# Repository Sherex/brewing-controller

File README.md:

# Brewing controller
A board to control a brewing-rig.

## Images
Temprature sensor ADCs and connectors to the TP100 elemts

230V current sensing, relay control and 230V to 12V/5V tranformer

3D render of temprature ADCs and connectors

## Development
Requires [KiCad EDA](https://kicad-pcb.org/)

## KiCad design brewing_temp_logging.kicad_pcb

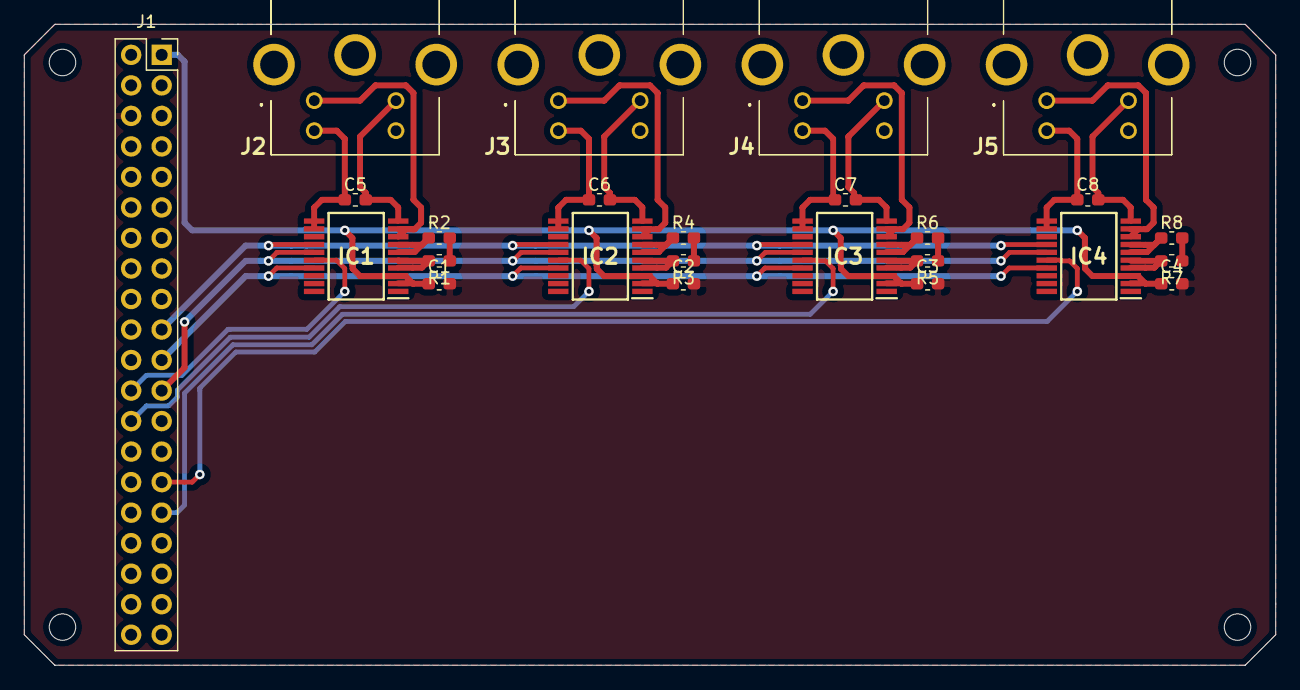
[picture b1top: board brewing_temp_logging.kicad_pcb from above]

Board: 2 copper layers, 104.1 x 53.3 mm, 25 parts (0 on the bottom side), 33 nets.

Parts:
C1, C5, C6, C7, C8: 100nF; C_0603_1608Metric_Pad1.05x0.95mm_HandSolder
C2, C3, C4: 0.1uF; C_0603_1608Metric_Pad1.05x0.95mm_HandSolder
IC1, IC2, IC3, IC4: MAX31865AAP+; SOP65P778X199-20N
J1: Raspberry_Pi_2_3_GPIO_PSU; PinSocket_2x20_P2.54mm_Vertical
J2, J3, J4, J5: Mini-DIN-4; MD40SM
R1, R3, R5, R7: 100R; R_0603_1608Metric_Pad1.05x0.95mm_HandSolder
R2, R4, R6, R8: 330R; R_0603_1608Metric_Pad1.05x0.95mm_HandSolder

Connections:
CE0: IC1.16, J1.24
CE1: IC2.16, J1.26
CE2: IC3.16, J1.31
CE3: IC4.16, J1.29
FORCE_W1_RTD1: IC1.8, IC1.9, J2.1
FORCE_W1_RTD2: IC2.8, IC2.9, J3.1
FORCE_W1_RTD3: IC3.8, IC3.9, J4.1
FORCE_W1_RTD4: IC4.8, IC4.9, J5.1
GND: C1.2, C2.2, C3.2, C4.2, IC1.13, IC1.18, IC1.19, IC2.13, IC2.18, IC2.19, IC3.13, IC3.18, IC3.19, IC4.13, IC4.18, IC4.19, J1.6
MISO: IC1.17, IC2.17, IC3.17, IC4.17, J1.21
MOSI: IC1.14, IC2.14, IC3.14, IC4.14, J1.19
unnamed: IC1.4, IC1.5, R1.2
unnamed: IC1.6, IC1.7, R2.2
unnamed: IC2.4, IC2.5, R3.2
unnamed: IC2.6, IC2.7, R4.2
unnamed: IC3.4, IC3.5, R5.2
unnamed: IC3.6, IC3.7, R6.2
unnamed: IC4.4, IC4.5, R7.2
unnamed: IC4.6, IC4.7, R8.2
unnamed: R1.1, R2.1
unnamed: R3.1, R4.1
unnamed: R5.1, R6.1
unnamed: R7.1, R8.1
RTDIN+_W2_RTD1: C5.1, IC1.10, J2.2
RTDIN+_W2_RTD2: C6.1, IC2.10, J3.2
RTDIN+_W2_RTD3: C7.1, IC3.10, J4.2
RTDIN+_W2_RTD4: C8.1, IC4.10, J5.2
RTDIN-_W3_RTD1: C5.2, IC1.11, IC1.12, J2.3
RTDIN-_W3_RTD2: C6.2, IC2.11, IC2.12, J3.3
RTDIN-_W3_RTD3: C7.2, IC3.11, IC3.12, J4.3
RTDIN-_W3_RTD4: C8.2, IC4.11, IC4.12, J5.3
SCLK: IC1.15, IC2.15, IC3.15, IC4.15, J1.23
VDD_3.3V: C1.1, C2.1, C3.1, C4.1, IC1.2, IC1.3, IC2.2, IC2.3, IC3.2, IC3.3, IC4.2, IC4.3, J1.1

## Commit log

2020-06-07 Create LICENSE
2020-06-07 Added images
